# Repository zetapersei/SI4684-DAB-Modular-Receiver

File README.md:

# Note:
The version in the repository is an ongoing development. It could and will contain bugs. To make sure you use the latest fully tested firmware, check the releases!

# SI4684 DAB receiver
Advanced DAB Tuner software for Skyworks SI4684 tuner with ESP32 board and a color LCD\
More information: https://www.pe5pvb.nl/

## Fork updates

### Modular receiver PCB
This fork adds a KiCad redesign for the **DAB+ receiver module A**. The board keeps the SI4684 tuner, 19.2 MHz reference, RF matching network, SMA antenna connector, and 1.8 V / 3.3 V regulation together as a dedicated receiver module. Its separate headers expose power, SPI, digital audio/control, and analog audio connections so the tuner can be integrated with the controller, display, and audio sections as distinct modules.

The KiCad source and reference outputs are in [`DAB_Module-Kicad/`](DAB_Module-Kicad/):
- `Dab+.kicad_sch` and `Dab+.kicad_pcb`: schematic and two-layer PCB.
- `schematic.pdf` and `layout.pdf`: exported design drawings.
- `Dab_bom.xlsx` and `BOM/`: bill of materials and component references.

Check the schematic for the exact connector pinout before wiring the modules: J1–J6 serve different signal groups, including the power rails (J3) and stereo analog output (J4). Do not assume the headers are interchangeable.

The checked-in `Dab+.csv` does not match this PCB revision (including connector and U3 details). Regenerate it from the current schematic and verify the U3 supplier part number before ordering components.

### Controller PCB
The controller board design is in [`Controller-Kicad/`](Controller-Kicad/). It brings together the DOIT ESP32 DevKit, TFT display, rotary encoders, and control buttons, with a `Mainboard` connector for the receiver module.

- `SI4684 controller SMD.kicad_sch`, `SI4684 controller SMD.kicad_pcb`, and `SI4684 controller SMD.kicad_pro`: schematic, PCB, and KiCad project.
- `Library.pretty/`: custom footprints for the ESP32 DevKit and TFT display, referenced by the project footprint library table.

Open the `.kicad_pro` project in KiCad to use its project-specific footprint configuration. Check the schematic for the `Mainboard` connector pinout before connecting it to the receiver module.

### Firmware modules
The firmware in `src/` is organized around the same functional boundaries:
- `si4684.*`: tuner control, DAB service data, and MOT slideshow reception.
- `comms.*`: serial command and status protocol.
- `gui.*`, `graphics.h`, `font.h`, and `language.h`: display, graphics, fonts, and localization.
- `slideshow.*` and `JPEGdecoder.*`: slideshow rendering.
- `IRReceiver.*` and `TPA6130A2.*`: remote input and headphone amplifier.

# Libraries
These are the libraries used for this project:
- https://github.com/Bodmer/TFT_eSPI
- https://github.com/Bodmer/JPEGDecoder
- https://github.com/bitbank2/PNGdec

Use these settings in the TFT_eSPI library:
```
#define ILI9341_DRIVER
#define TFT_CS          5
#define TFT_DC          4
#define TFT_RST         17
#define SPI_FREQUENCY   50000000
#define SMOOTH_FONT
```
# Buttons
A brief instruction for the buttons:
- Top encoder: Choose frequency or memory channel
- Bottom encoder: Choose service or set headphones volume
- Top button: Short press: Service information, Long press: Stand-by mode.
- Middle button: Short press: Set mode, Long press: Open menu.
- Lower button: Toggle Slideshow view.
  
## Contributing
I'm open for a new ideas in our project. Feel free to share your thoughts in [Discussions](https://github.com/PE5PVB/SI4684-DAB-Receiver/discussions).\
You can also contribute your own code using [Pull Requests](https://github.com/PE5PVB/SI4684-DAB-Receiver/pulls). We will review it and merge into main branch.

You are using my software and you found a difficulty? Please create new [issue](https://github.com/PE5PVB/SI4684-DAB-Receiver/issues) and describe your problem.

I also would like to invite you to join our Discord community where we share our ideas and help each other with some issues.\

Special thanks to all [contributors](https://github.com/PE5PVB/TEF-Nextion-Multiband/graphs/contributors). You are awesome! ❤️
## License
This program is free software; you can redistribute it and/or modify it under the terms of the GNU General Public License as published by the Free Software Foundation; either version 3 of the License, or (at your option) any later version.

This program is distributed in the hope that it will be useful, but WITHOUT ANY WARRANTY; without even the implied warranty of MERCHANTABILITY or FITNESS FOR A PARTICULAR PURPOSE. See the GNU General Public License for more details. 

## If you like this software

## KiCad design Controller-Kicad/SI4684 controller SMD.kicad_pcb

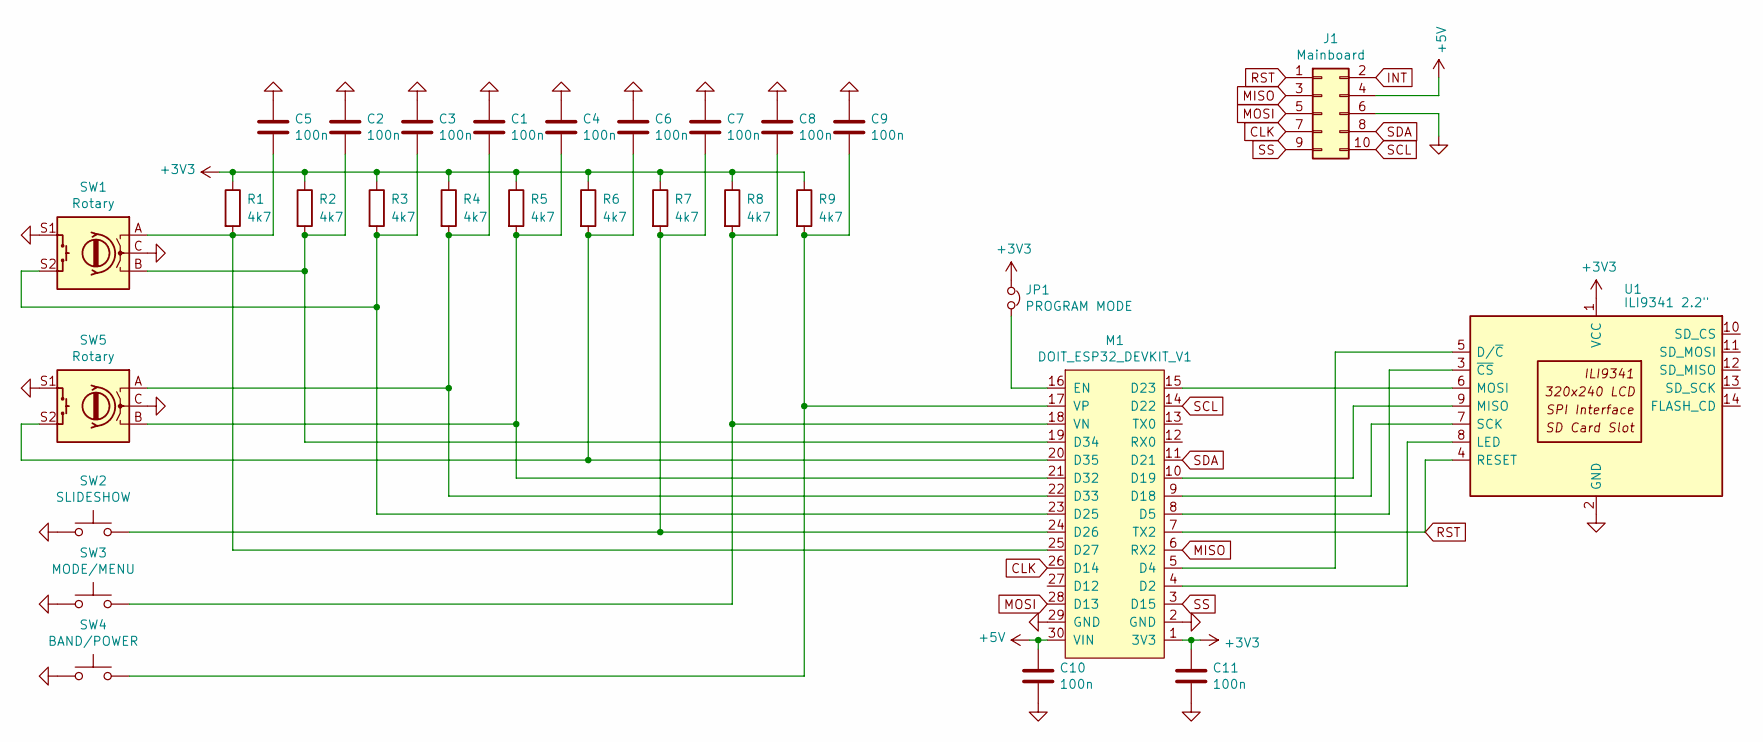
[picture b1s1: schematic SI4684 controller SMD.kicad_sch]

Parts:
C1, C2, C3, C4, C5, C6, C7, C8, C9, C10, C11: 100n; C_1206_3216Metric
J1: Mainboard; IDC-Header_2x05_P2.54mm_Vertical
JP1: PROGRAM MODE; TestPoint_2Pads_Pitch2.54mm_Drill0.8mm
M1: DOIT_ESP32_DEVKIT_V1; ESP32_DOIT_DEVKIT_V1
R1, R2, R3, R4, R5, R6, R7, R8, R9: 4k7; R_1206_3216Metric
SW1, SW5: Rotary; RotaryEncoder_Alps_EC11E-Switch_Vertical_H20mm
SW2: SLIDESHOW; SW_PUSH_6mm_H7.3mm
SW3: MODE/MENU; SW_PUSH_6mm_H7.3mm
SW4: BAND/POWER; SW_PUSH_6mm_H7.3mm
U1: ILI9341 2.2"; CR2013-MI2120

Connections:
+3V3: C11.1, JP1.1, M1.1 (3V3), R1.1, R2.1, R3.1, R4.1, R5.1, R6.1, R7.1, R8.1, R9.1, U1.1 (VCC)
+5V: C10.1, J1.4, M1.30 (VIN)
CLK: J1.7, M1.26 (D14)
GND: C1.1, C2.1, C3.1, C4.1, C5.1, C6.1, C7.1, C8.1, C9.1, C10.2, C11.2, J1.6, M1.2 (GND), M1.29 (GND), SW1.C, SW1.S1, SW2.1, SW3.1, SW4.1, SW5.C, SW5.S1, U1.2 (GND)
INT: J1.2
MISO: J1.3, M1.6 (RX2)
MOSI: J1.5, M1.28 (D13)
unnamed: M1.4 (D2), U1.8 (LED)
unnamed: M1.5 (D4), U1.5 (D/~C)
unnamed: M1.8 (D5), U1.3 (~CS)
unnamed: M1.9 (D18), U1.7 (SCK)
unnamed: M1.10 (D19), U1.9 (MISO)
unnamed: M1.15 (D23), U1.6 (MOSI)
unnamed: C3.2, M1.23 (D25), R3.2, SW1.S2
unnamed: C7.2, M1.24 (D26), R7.2, SW2.2
unnamed: C5.2, M1.25 (D27), R1.2, SW1.A
unnamed: C4.2, M1.21 (D32), R5.2, SW5.B
unnamed: C1.2, M1.22 (D33), R4.2, SW5.A
unnamed: C2.2, M1.19 (D34), R2.2, SW1.B
unnamed: C6.2, M1.20 (D35), R6.2, SW5.S2
unnamed: JP1.2, M1.16 (EN)
unnamed: C8.2, M1.18 (VN), R8.2, SW3.2
unnamed: C9.2, M1.17 (VP), R9.2, SW4.2
RST: J1.1, M1.7 (TX2), U1.4 (RESET)
SCL: J1.10, M1.14 (D22)
SDA: J1.8, M1.11 (D21)
SS: J1.9, M1.3 (D15)

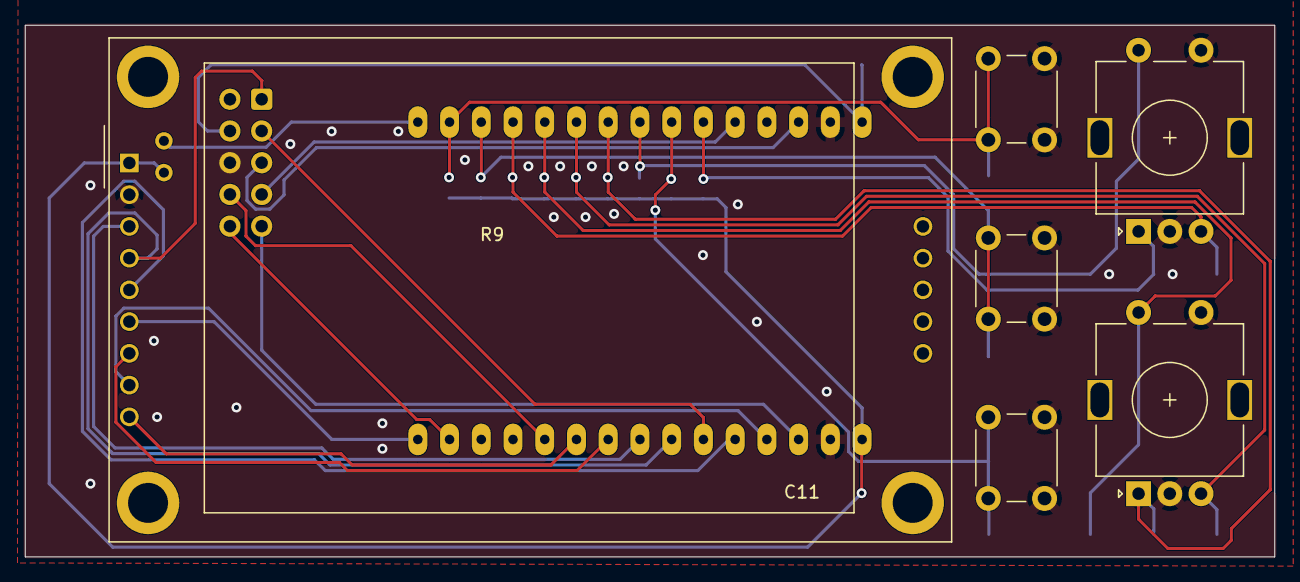
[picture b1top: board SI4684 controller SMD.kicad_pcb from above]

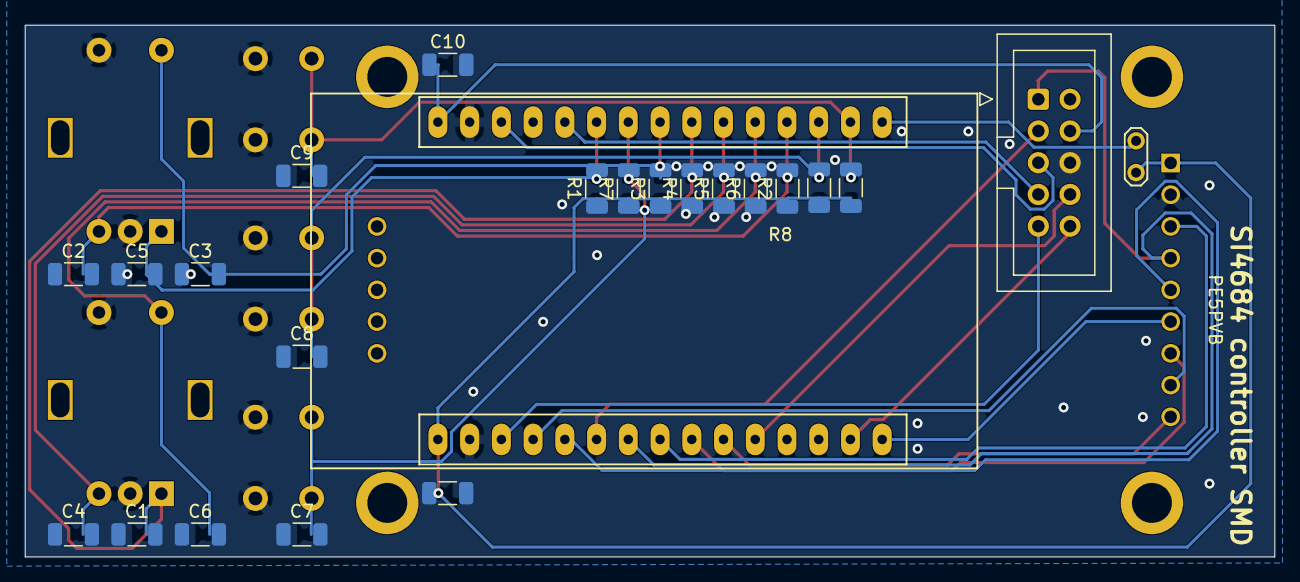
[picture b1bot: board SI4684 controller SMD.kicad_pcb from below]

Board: 2 copper layers, 100.0 x 42.5 mm, 29 parts (23 on the bottom side), 26 nets.

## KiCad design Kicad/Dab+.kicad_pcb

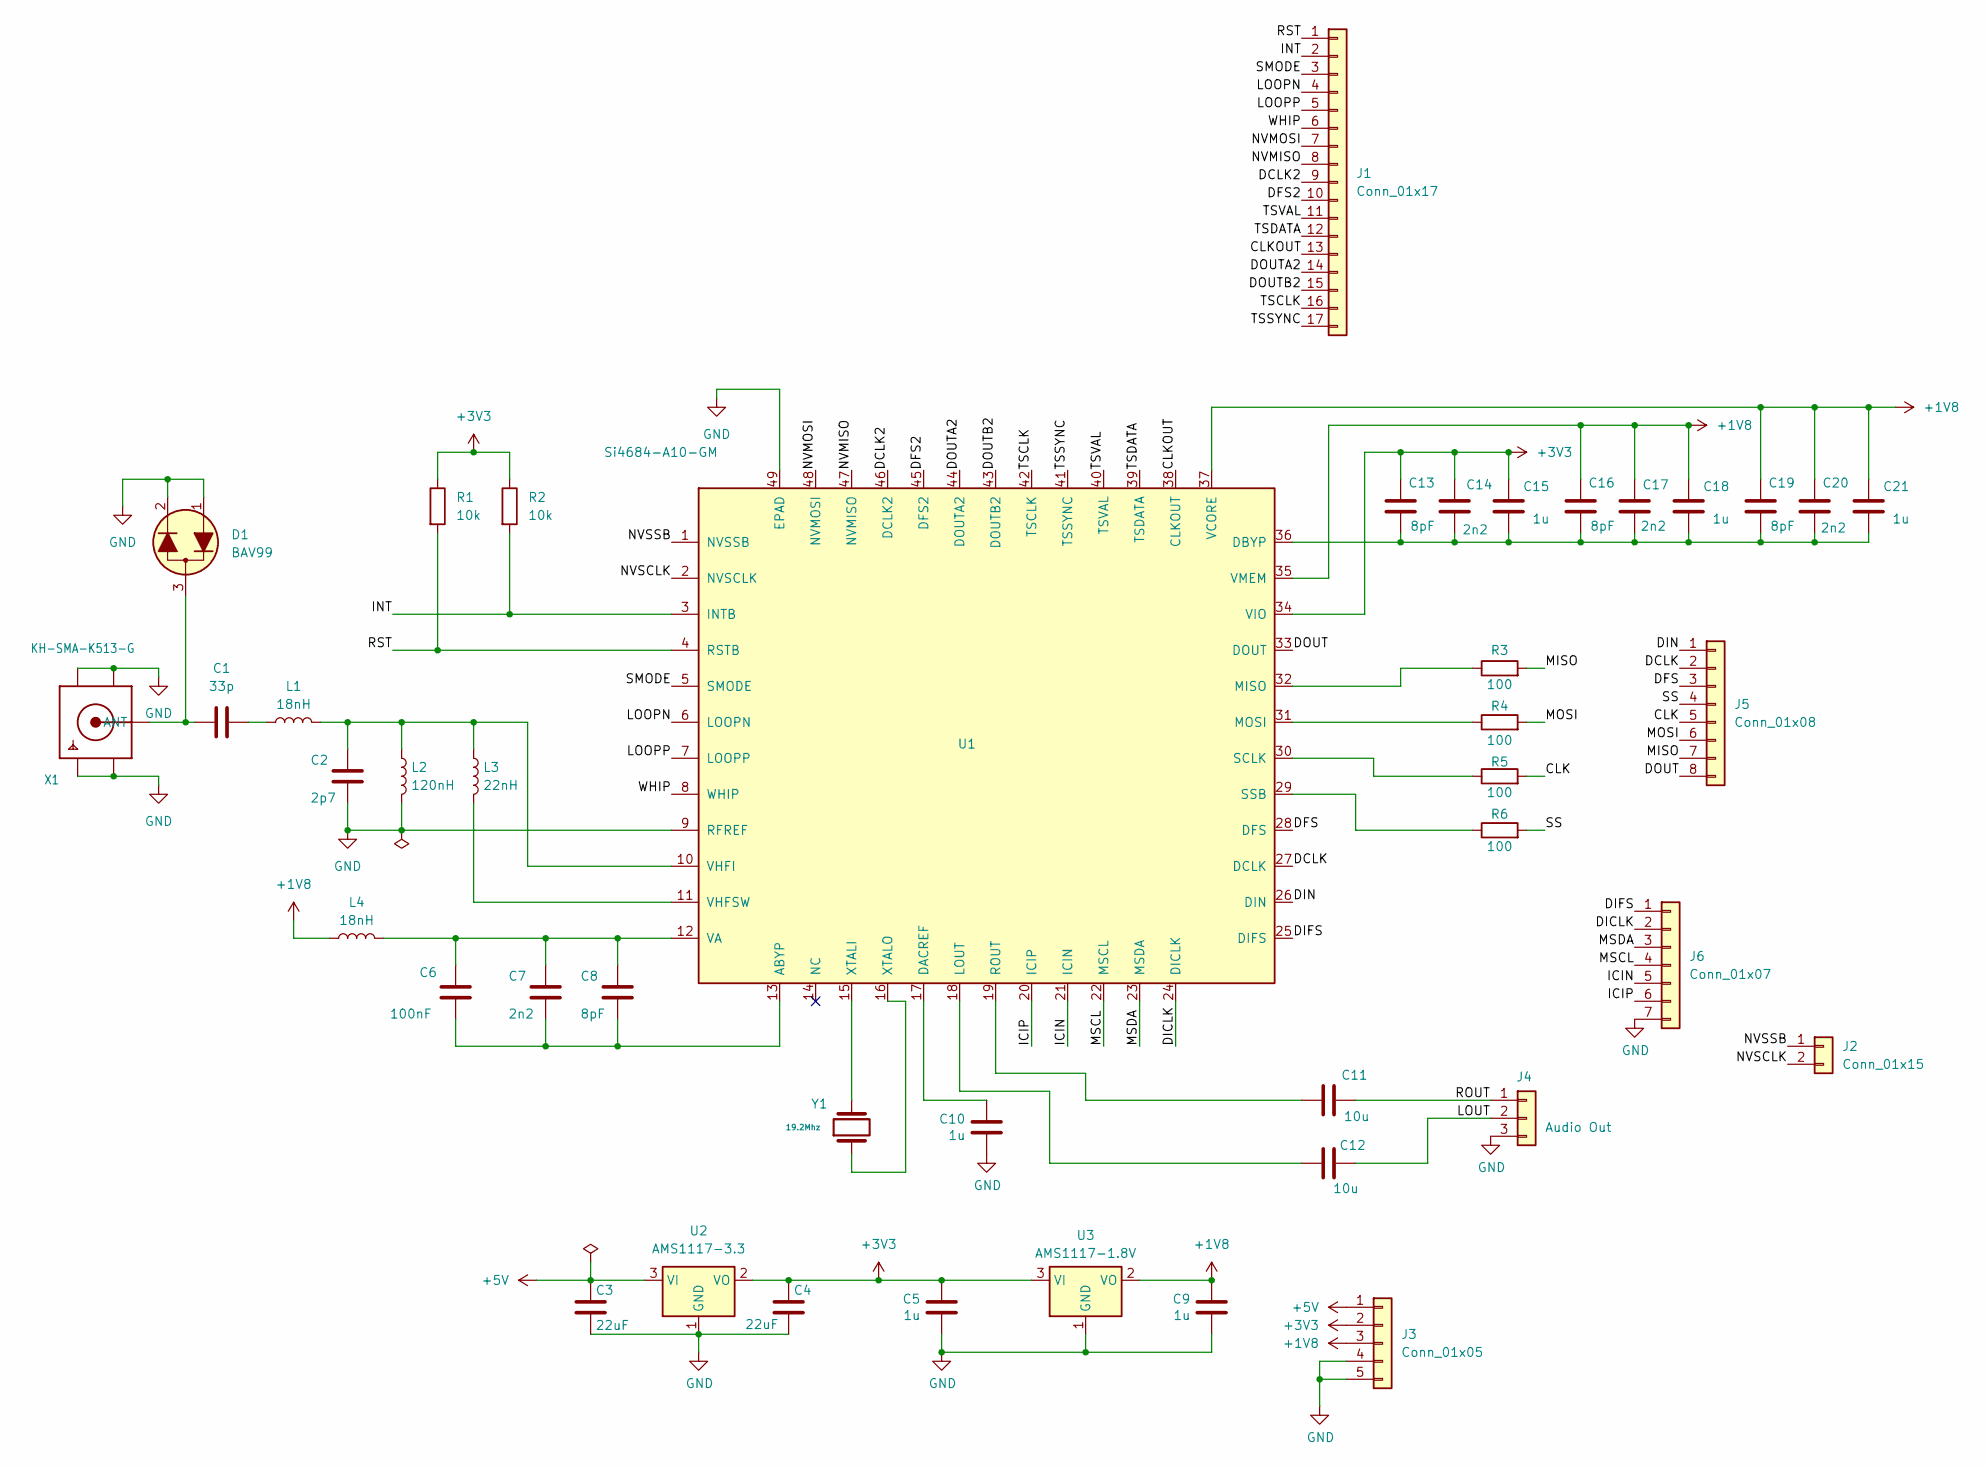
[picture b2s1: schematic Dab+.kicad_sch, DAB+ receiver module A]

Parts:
C1: 33p; C_0805_2012Metric; LCSC C1562
C2: 2p7; C_0805_2012Metric; LCSC C1650
C3, C4: 22uF; C_0805_2012Metric; LCSC C59461
C5, C9, C10, C15, C18, C21: 1u; C_0805_2012Metric; LCSC C52923
C6: 100nF; C_0805_2012Metric; LCSC C1525
C7, C14, C17, C20: 2n2; C_0805_2012Metric; LCSC C1604
C8, C13, C16, C19: 8pF; C_0805_2012Metric; LCSC C1578
C11, C12: 10u; C_0805_2012Metric; LCSC C96446
D1: BAV99; SOT-23; LCSC C2500
J1: Conn_01x17; PinHeader_1x17_P2.54mm_Vertical
J2: Conn_01x15; PinHeader_1x02_P2.54mm_Vertical
J3: Conn_01x05; PinHeader_1x05_P2.54mm_Vertical
J4: Audio Out; PinHeader_1x03_P2.54mm_Vertical
J5: Conn_01x08; PinHeader_1x08_P2.54mm_Vertical
J6: Conn_01x07; PinHeader_1x07_P2.54mm_Vertical
L1, L4: 18nH; L_0805_2012Metric; LCSC C86060
L2: 120nH; L_0805_2012Metric_Pad1.15x1.40mm_HandSolder; LCSC C405042
L3: 22nH; L_0805_2012Metric; LCSC C15178
R1, R2: 10k; R_0805_2012Metric; LCSC C25744
R3, R4, R5, R6: 100; R_0805_2012Metric; LCSC C25076
U1: Si4684-A10-GM; QFN-48-1EP_7x7mm_long_term
U2: AMS1117-3.3; SOT-223-3_TabPin2; LCSC C6186
U3: AMS1117-1.8V; SOT-223-3_TabPin2; LCSC C626116
X1: KH-SMA-K513-G; SMA_Amphenol_901-143_Horizontal_modified
Y1: 19.2Mhz; Crystal_SMD_HC49-SD; LCSC C654977

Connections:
+1V8: C9.1, C16.1, C17.1, C18.1, C19.1, C20.1, C21.1, J3.3, L4.1, U1.35 (VMEM), U1.37 (VCORE), U3.2 (VO)
+3V3: C4.1, C5.1, C13.1, C14.1, C15.1, J3.2, R1.1, R2.1, U1.34 (VIO), U2.2 (VO), U3.3 (VI)
+5V: C3.1, J3.1, U2.3 (VI)
/CLK: J5.5, R5.2
/CLKOUT: J1.13, U1.38 (CLKOUT)
/DCLK: J5.2, U1.27 (DCLK)
/DCLK2: J1.9, U1.46 (DCLK2)
/DFS: J5.3, U1.28 (DFS)
/DFS2: J1.10, U1.45 (DFS2)
/DICLK: J6.2, U1.24 (DICLK)
/DIFS: J6.1, U1.25 (DIFS)
/DIN: J5.1, U1.26 (DIN)
/DOUT: J5.8, U1.33 (DOUT)
/DOUTA2: J1.14, U1.44 (DOUTA2)
/DOUTB2: J1.15, U1.43 (DOUTB2)
/ICIN: J6.5, U1.21 (ICIN)
/ICIP: J6.6, U1.20 (ICIP)
/INT: J1.2, R2.2, U1.3 (INTB)
/LOOPN: J1.4, U1.6 (LOOPN)
/LOOPP: J1.5, U1.7 (LOOPP)
/LOUT: C12.2, J4.2
/MISO: J5.7, R3.2
/MOSI: J5.6, R4.2
/MSCL: J6.4, U1.22 (MSCL)
/MSDA: J6.3, U1.23 (MSDA)
/NVMISO: J1.8, U1.47 (NVMISO)
/NVMOSI: J1.7, U1.48 (NVMOSI)
/NVSCLK: J2.2, U1.2 (NVSCLK)
/NVSSB: J2.1, U1.1 (NVSSB)
/ROUT: C11.2, J4.1
/RST: J1.1, R1.2, U1.4 (RSTB)
/SMODE: J1.3, U1.5 (SMODE)
/SS: J5.4, R6.2
/TSCLK: J1.16, U1.42 (TSCLK)
/TSDATA: J1.12, U1.39 (TSDATA)
/TSSYNC: J1.17, U1.41 (TSSYNC)
/TSVAL: J1.11, U1.40 (TSVAL)
/WHIP: J1.6, U1.8 (WHIP)
GND: C2.2, C3.2, C4.2, C5.2, C9.2, C10.2, D1.1 (A), D1.2 (K), J3.4, J3.5, J4.3, J6.7, L2.2, U1.9 (RFREF), U1.49 (EPAD), U2.1 (GND), U3.1 (GND), X1.2 (GND1)
unnamed: C1.2, L1.1
unnamed: C1.1, D1.3 (C), X1.1 (ANT)
unnamed: C6.1, C7.2, C8.2, U1.13 (ABYP)
unnamed: C10.1, U1.17 (DACREF)
unnamed: C13.2, C14.2, C15.2, C16.2, C17.2, C18.2, C19.2, C20.2, C21.2, U1.36 (DBYP)
unnamed: C12.1, U1.18 (LOUT)
unnamed: R3.1, U1.32 (MISO)
unnamed: R4.1, U1.31 (MOSI)
unnamed: C11.1, U1.19 (ROUT)
unnamed: R5.1, U1.30 (SCLK)
unnamed: R6.1, U1.29 (SSB)
unnamed: C6.2, C7.1, C8.1, L4.2, U1.12 (VA)
unnamed: C2.1, L1.2, L2.1, L3.1, U1.10 (VHFI)
unnamed: L3.2, U1.11 (VHFSW)
unnamed: U1.15 (XTALI), Y1.2
unnamed: U1.16 (XTALO), Y1.1

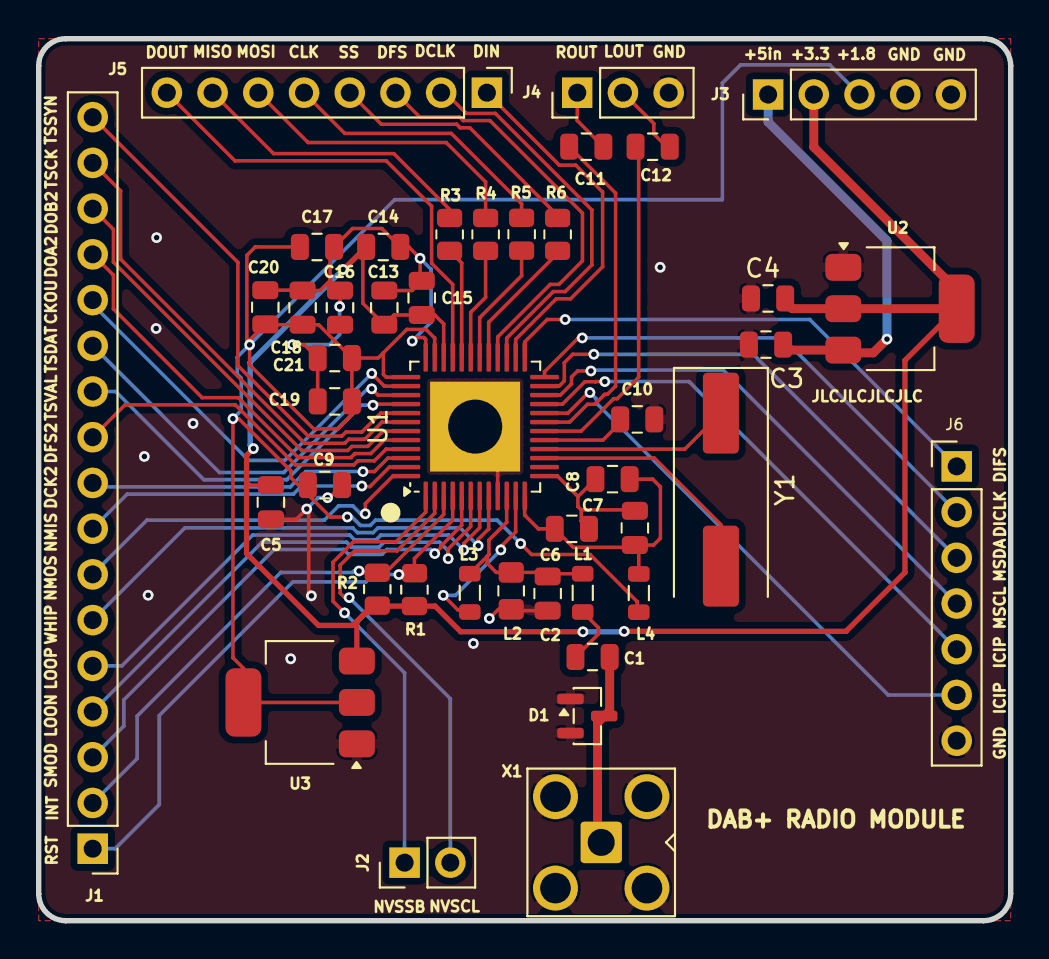
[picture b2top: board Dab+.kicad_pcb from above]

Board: 2 copper layers, 54.0 x 49.0 mm, 43 parts (0 on the bottom side), 55 nets.

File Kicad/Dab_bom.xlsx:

Comment | Designator | Footprint | JLCPCB Part#
33p | C1 | Capacitor_SMD:C_0402_1005Metric | C1562
2p7 | C2 | Capacitor_SMD:C_0603_1608Metric | C1650
22uF | C3,C4 | Capacitor_SMD:C_0603_1608Metric | C59461
1u | C5,C9,C10,C15,C18,C21 | Capacitor_SMD:C_0402_1005Metric | C52923
100nF | C6 | Capacitor_SMD:C_0402_1005Metric | C1525
2n2 | C7,C14,C17,C20 | Capacitor_SMD:C_0603_1608Metric | C1604
8pF | C8,C13,C16,C19 | Capacitor_SMD:C_0402_1005Metric | C1578
10u | C11,C12 | Capacitor_SMD:C_0603_1608Metric | C96446
BAV99 | D1 | Package_TO_SOT_SMD:SOT-23 | C2500
18nH | L1,L4 | Inductor_SMD:L_0402_1005Metric | C86060
120nH | L2 | Inductor_SMD:L_0402_1005Metric | C405042
22nH | L3 | Inductor_SMD:L_0402_1005Metric | C15178
10k | R1,R2 | Resistor_SMD:R_0402_1005Metric | C25744
100 | R3,R4,R5,R6 | Resistor_SMD:R_0402_1005Metric | C25076
AMS1117-3.3 | U2 | Package_TO_SOT_SMD:SOT-223-3_TabPin2 | C6186
MIC5504-1.8YM5 | U3 | Package_TO_SOT_SMD:SOT-23-5 | C626116
19.2Mhz | Y1 | Crystal:Crystal_SMD_3225-4Pin_3.2x2.5mm | C654977

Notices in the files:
README.md:
https://img.shields.io/badge/license%20-%20GNU_GPLv3-GPLv3?color=blue
